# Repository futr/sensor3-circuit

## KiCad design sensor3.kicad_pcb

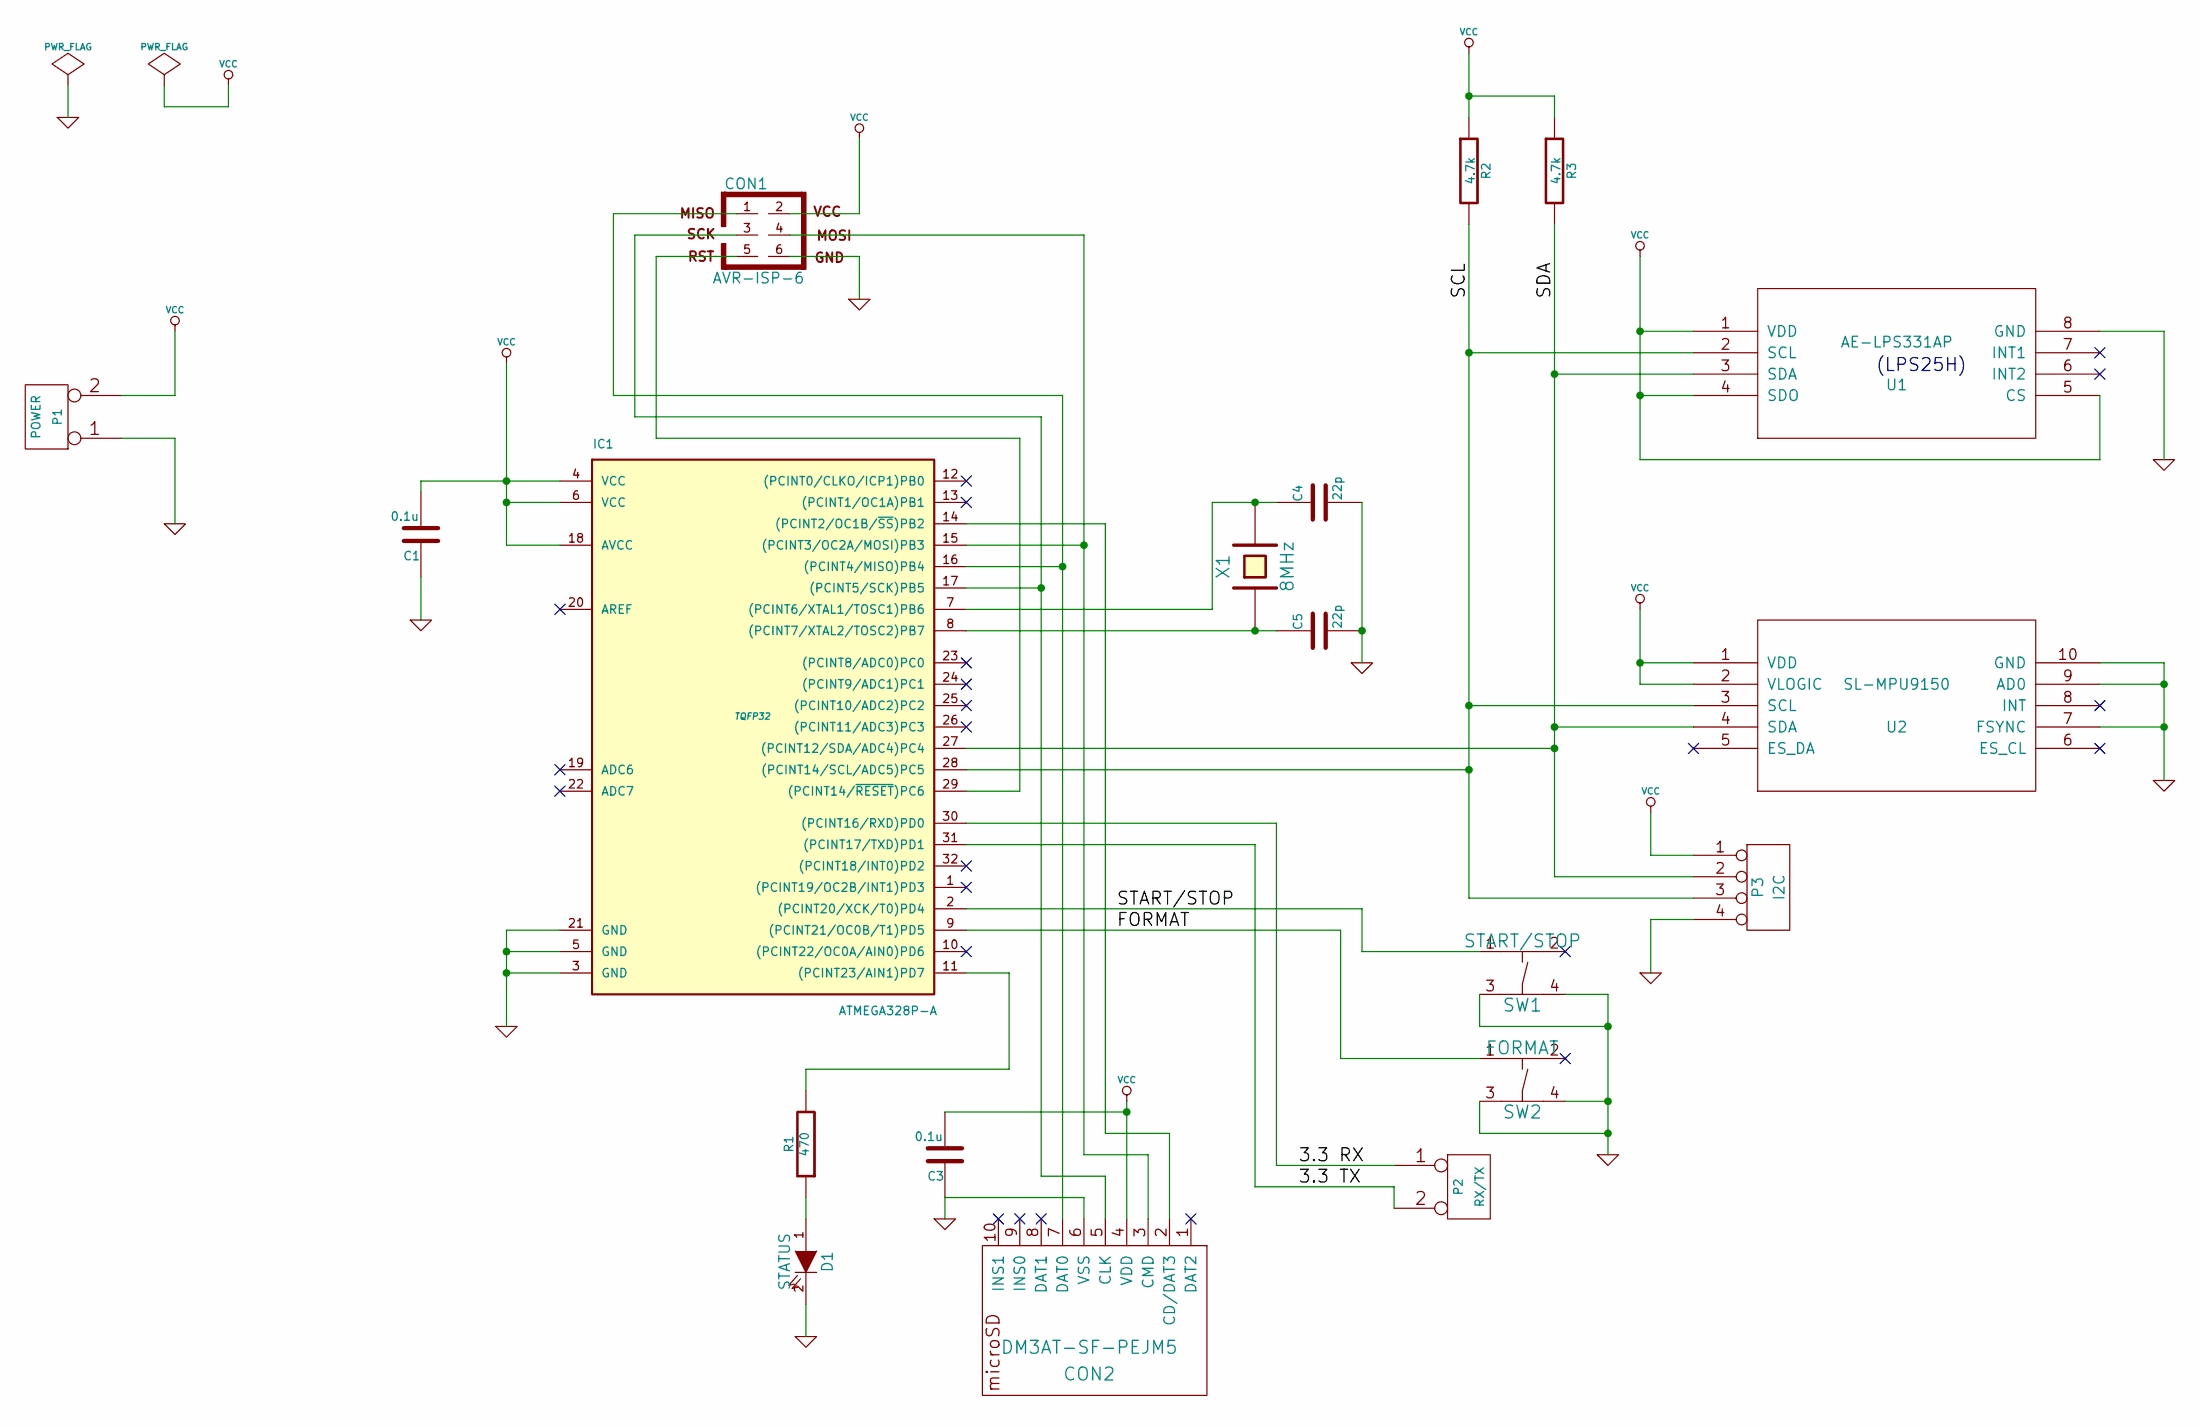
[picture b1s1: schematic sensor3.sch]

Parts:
C1, C3: 0.1u
C4, C5: 22p
CON1: AVR-ISP-6
CON2: DM3AT-SF-PEJM5
D1: STATUS
IC1: ATMEGA328P-A; TQFP32
P1: POWER
P2: RX/TX
P3: I2C
R1: 470
R2, R3: 4.7k
SW1: START/STOP
SW2: FORMAT
U1: AE-LPS331AP; MODULE
U2: SL-MPU9150; MODULE
X1: 8MHz

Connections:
/3.3 RX: IC1.30 ((PCINT16/RXD)PD0), P2.1
/3.3 TX: IC1.31 ((PCINT17/TXD)PD1), P2.2 (PM)
/FORMAT: IC1.9 ((PCINT21/OC0B/T1)PD5), SW2.1
/SCL: IC1.28 ((PCINT14/SCL/ADC5)PC5), P3.3, R2.2, U1.2 (SCL), U2.3 (SCL)
/SDA: IC1.27 ((PCINT12/SDA/ADC4)PC4), P3.2, R3.2, U1.3 (SDA), U2.4 (SDA)
/START/STOP: IC1.2 ((PCINT20/XCK/T0)PD4), SW1.1
GND: C1.1, C3.1, C4.2, C5.2, CON1.6, CON2.6 (VSS), D1.2 (K), IC1.3 (GND), IC1.5 (GND), IC1.21 (GND), P1.1, P3.4, SW1.3, SW1.4, SW2.3, SW2.4, U1.8 (GND), U2.7 (FSYNC), U2.9 (AD0), U2.10 (GND)
unnamed: CON2.2 (CD/DAT3), IC1.14 ((PCINT2/OC1B/~SS~)PB2)
unnamed: IC1.11 ((PCINT23/AIN1)PD7), R1.2
unnamed: D1.1 (A), R1.1
unnamed: C5.1, IC1.8 ((PCINT7/XTAL2/TOSC2)PB7), X1.1
unnamed: C4.1, IC1.7 ((PCINT6/XTAL1/TOSC1)PB6), X1.2
unnamed: CON1.5, IC1.29 ((PCINT14/~RESET~)PC6)
unnamed: CON1.4, CON2.3 (CMD), IC1.15 ((PCINT3/OC2A/MOSI)PB3)
unnamed: CON1.1, CON2.7 (DAT0), IC1.16 ((PCINT4/MISO)PB4)
unnamed: CON1.3, CON2.5 (CLK), IC1.17 ((PCINT5/SCK)PB5)
VCC: C1.2, C3.2, CON1.2, CON2.4 (VDD), IC1.4 (VCC), IC1.6 (VCC), IC1.18 (AVCC), P1.2 (PM), P3.1, R2.1, R3.1, U1.1 (VDD), U1.4 (SDO), U1.5 (CS), U2.1 (VDD), U2.2 (VLOGIC)

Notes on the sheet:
(LPS25H)

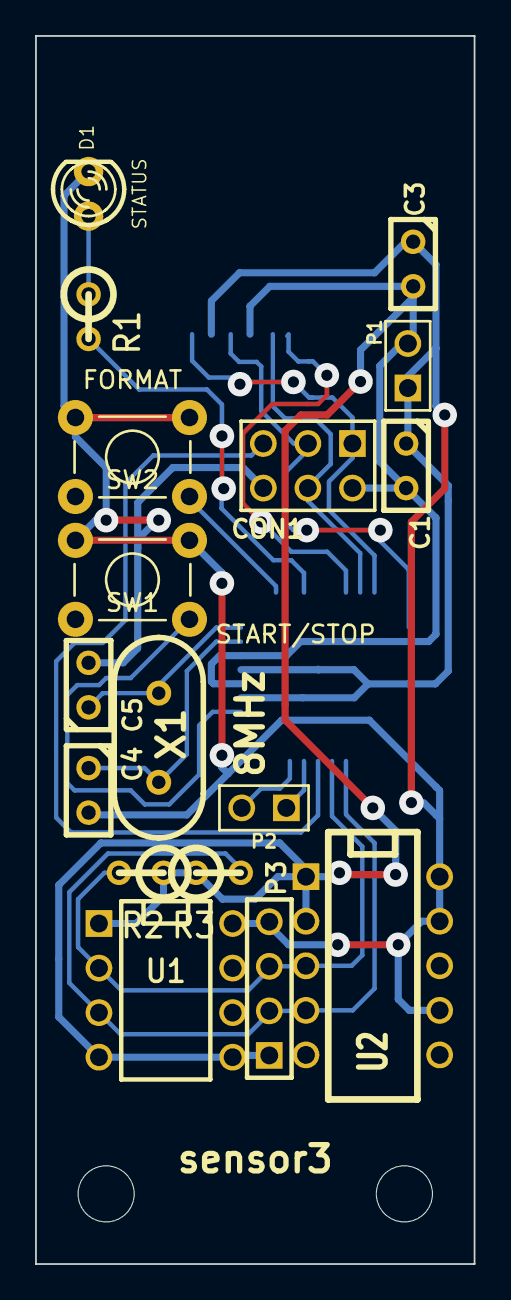
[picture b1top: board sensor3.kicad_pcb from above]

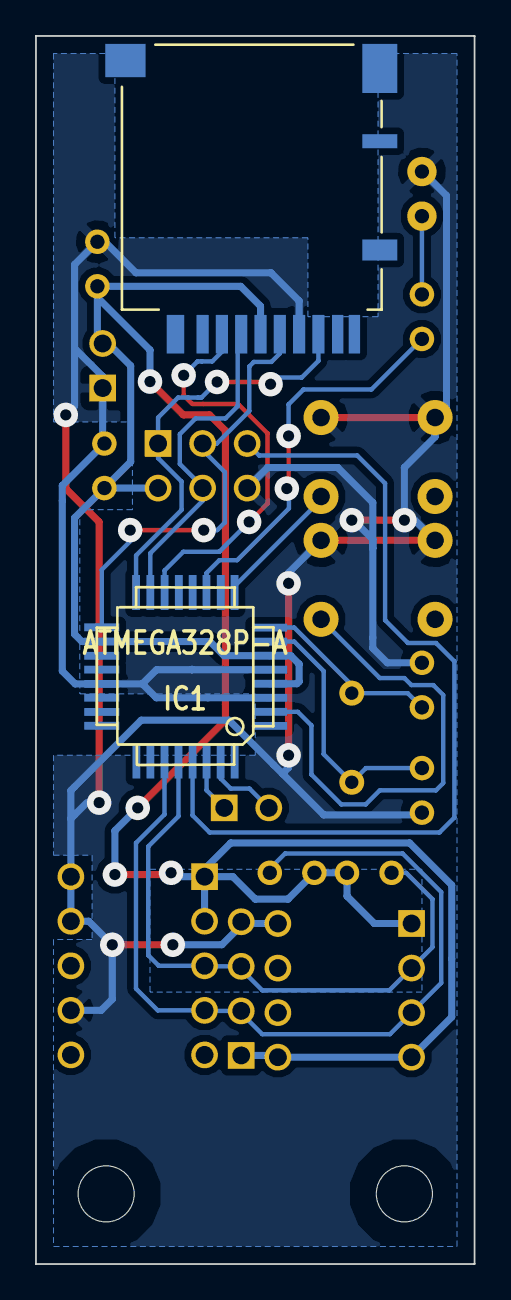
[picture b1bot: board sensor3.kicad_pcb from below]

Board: 2 copper layers, 25.0 x 70.0 mm, 21 parts (2 on the bottom side), 17 nets.

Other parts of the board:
hole3-2mm, hole3-2mm#2: VAL**; hole3-2mm

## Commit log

2015-01-22 Add pdf of circuit
2015-01-27 Modify for halfside
2015-01-28 Up via width
2015-01-28 Connect FSYNC to GND
2015-01-28 Change pad size and line width for MITS
2015-01-29 Update pdf
2015-02-11 Release halfside
2015-02-11 Remove PDF
2015-02-11 Remove doc/ from gitignore
